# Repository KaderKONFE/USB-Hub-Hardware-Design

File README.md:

# USB Hub Hardware & PCB Design

This repository contains the schematic and PCB design for a high-speed USB Hub, developed according to industrial design rules and signal integrity standards.

## Tech Stack & Tools
* **CAD Software:** KiCad
* **Design Type:** Schematic Capture & PCB Layout
* **Key Focus:** Signal integrity, power management, and protection circuits.

## Features
* Designed high-speed USB data lines with proper impedance matching.
* Integrated power management and circuit protection elements.

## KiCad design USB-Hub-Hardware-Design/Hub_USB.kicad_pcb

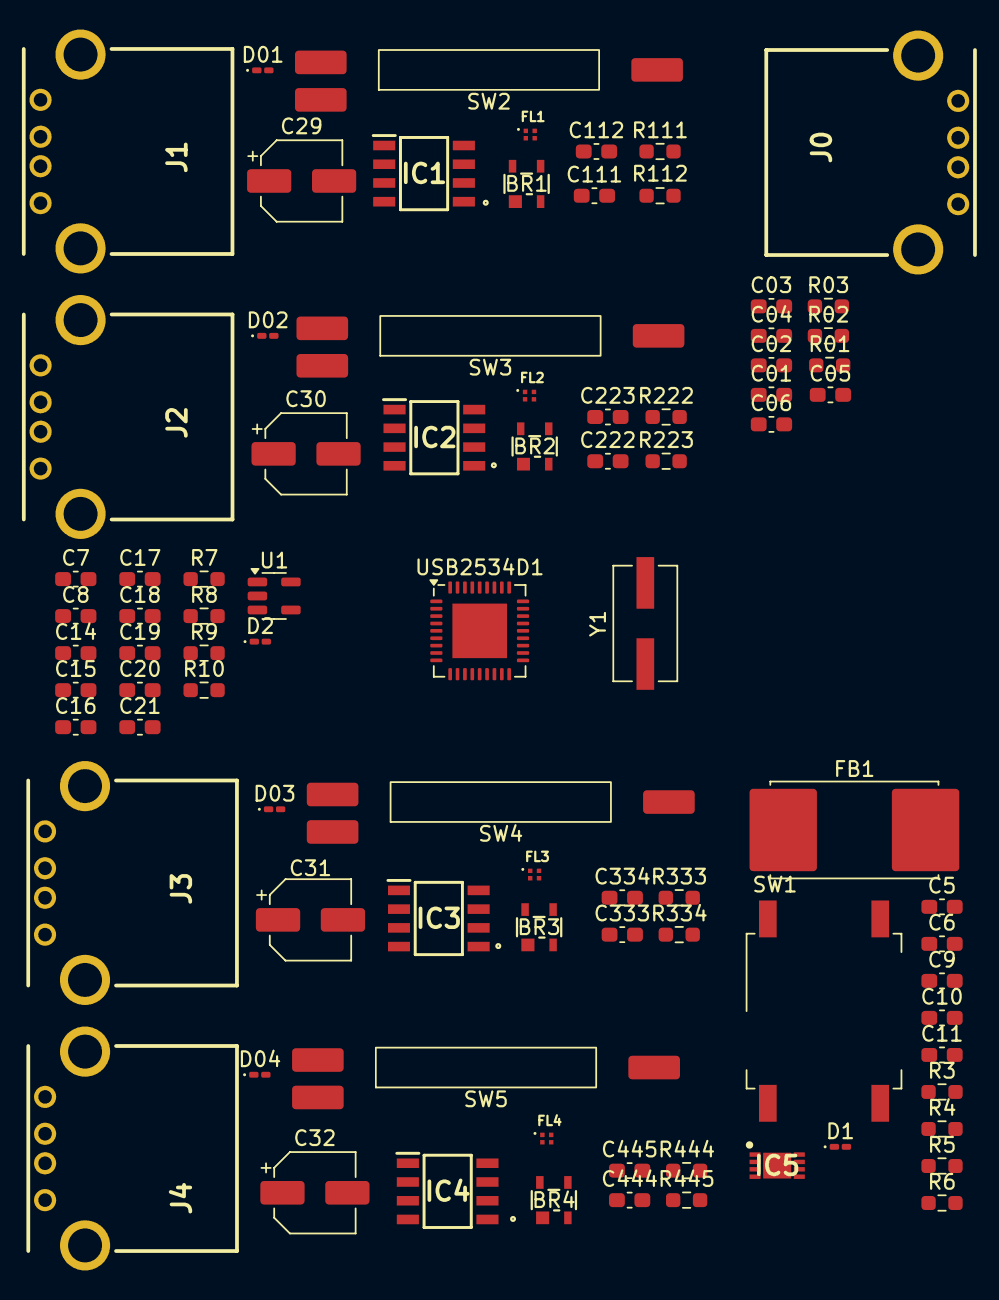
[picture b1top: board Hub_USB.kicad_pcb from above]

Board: 2 copper layers, 85 parts (0 on the bottom side), 45 nets, no tracks yet.

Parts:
BR1, BR2, BR3, BR4: BGX50AE6327HTSA1
C01: 10uF; C_0603_1608Metric_Pad1.08x0.95mm_HandSolder
C02, C5, C06, C6, C14, C16, C17, C19, C20, C111, C112, C222, C223, C333, C334, C444, C445: 0.1uF; C_0603_1608Metric_Pad1.08x0.95mm_HandSolder
C03: 2.2uF; C_0603_1608Metric_Pad1.08x0.95mm_HandSolder
C04: 1nF; C_0603_1608Metric_Pad1.08x0.95mm_HandSolder
C05, C9: 1.0nF; C_0603_1608Metric_Pad1.08x0.95mm_HandSolder
C7, C8: 6pF; C_0603_1608Metric_Pad1.08x0.95mm_HandSolder
C10, C11, C15, C18, C21: 4.7uF; C_0603_1608Metric_Pad1.08x0.95mm_HandSolder
C29, C30, C31, C32: 150uF; CP_Elec_5x5.7
D01, D1, D02, D2, D03, D04: LED; LED_0201_0603Metric_Pad0.64x0.40mm_HandSolder
FB1: 2A/0.05DCR; L_Vishay_IHSM-3825
FL1, FL2, FL3, FL4: DLM0NSM900HY2D
IC1, IC2, IC3, IC4: AP2111SG-13
IC5: MCP1725-ADJE_MC
J0, J1, J2, J3, J4: 614004190021
R01, R3, R111, R112, R222, R223, R333, R334, R444, R445: 330; R_0603_1608Metric_Pad0.98x0.95mm_HandSolder
R02, R10: 100K; R_0603_1608Metric_Pad0.98x0.95mm_HandSolder
R03: 50K; R_0603_1608Metric_Pad0.98x0.95mm_HandSolder
R4: 150K; R_0603_1608Metric_Pad0.98x0.95mm_HandSolder
R5: 21.0K; R_0603_1608Metric_Pad0.98x0.95mm_HandSolder
R6, R8: 10K; R_0603_1608Metric_Pad0.98x0.95mm_HandSolder
R7: 12.0K; R_0603_1608Metric_Pad0.98x0.95mm_HandSolder
R9: 1K; R_0603_1608Metric_Pad0.98x0.95mm_HandSolder
SW1: SW_MEC_5G; SW_MEC_5GSH9
SW2, SW3, SW4, SW5: SW_SPDT; SW_SPDT_REED_MSDM-DT
U1: 74LVC1G14; SOT-23-5
USB2534D1: QFN-36-1EP_6x6mm_P0.5mm_EP3.7x3.7mm
Y1: 24MHz; Crystal_SMD_ECS_CSM3X-2Pin_7.6x4.1mm

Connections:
+3V3: C6.1, C9.1, C11.1, C14.2, C15.2, C16.2, C17.2, C18.2, C19.2, C20.2, IC5.8 (VOUT), R3.1, R4.1, R10.2, U1.3 (GND), USB2534D1.10 (VDDA33), USB2534D1.11 (FLEX_IN), USB2534D1.15 (VDD33), USB2534D1.23 (VDD33), USB2534D1.29 (VDDA33), USB2534D1.36 (VDDA33)
+5V: FB1.1, IC1.2 (IN_1), IC1.3 (IN_2), IC2.2 (IN_1), IC2.3 (IN_2), IC3.2 (IN_1), IC3.3 (IN_2), IC4.2 (IN_1), IC4.3 (IN_2), SW2.2 (B), SW3.2 (B), SW4.2 (B), SW5.2 (B)
/Connectors/EN1: IC1.4 (EN), SW2.1 (A)
/Connectors/EN2: IC2.4 (EN), SW3.1 (A)
/Connectors/EN3: IC3.4 (EN), SW4.1 (A)
/Connectors/EN4: IC4.4 (EN), SW5.1 (A)
/Connectors/PWR1: BR1.1, C29.2, C112.2, IC1.6 (OUT_1), IC1.7 (OUT_2), J1.1, R111.1
/Connectors/PWR2: BR2.1, C30.2, C223.2, IC2.6 (OUT_1), IC2.7 (OUT_2), J2.1, R222.1
/Connectors/PWR3: BR3.1, C31.2, C334.2, IC3.6 (OUT_1), IC3.7 (OUT_2), J3.1, R333.1
/Connectors/PWR4: BR4.1, C32.2, C445.2, IC4.6 (OUT_1), IC4.7 (OUT_2), J4.1, R444.1
/Core/XTAL1: C7.2, USB2534D1.33 (XTAL1/REFCLK), Y1.2
/Core/XTAL2: C8.2, USB2534D1.32 (XTAL2), Y1.1
DWNSTRM1-D_N: BR1.4, FL1.3, FL1.4, J1.2, USB2534D1.1 (SWAP_USBDN1_DM)
DWNSTRM1-D_P: BR1.2, FL1.1, FL1.2, J1.3, USB2534D1.2 (SWAP_USBDN1_DP)
DWNSTRM2-D_N: BR2.4, FL2.3, FL2.4, J2.2, USB2534D1.3 (USBDN2_DM)
DWNSTRM2-D_P: BR2.2, FL2.1, FL2.2, J2.3, USB2534D1.4 (USBDN2_DP)
DWNSTRM3-D_N: BR3.4, FL3.3, FL3.4, J3.2, USB2534D1.6 (USBDN3_DM)
DWNSTRM3-D_P: BR3.2, FL3.1, FL3.2, J3.3, USB2534D1.7 (USBDN3_DP)
DWNSTRM4-D_N: BR4.4, FL4.3, FL4.4, J4.2, USB2534D1.8 (USBDN4_DM)
DWNSTRM4-D_P: BR4.2, FL4.1, FL4.2, J4.3, USB2534D1.9 (USBDN4_DP)
GND: BR1.3, BR2.3, BR3.3, BR4.3, C01.2, C02.2, C03.2, C04.2, C5.2, C06.1, C6.2, C7.1, C8.1, C9.2, C10.2, C11.2, C14.1, C15.1, C16.1, C17.1, C18.1, C19.1, C20.1, C21.1, C111.1, C112.1, C222.1, C223.1, C333.1, C334.1, C444.1, C445.1, D01.1 (K), D1.1 (K), D02.1 (K), D2.1 (K), D03.1 (K), D04.1 (K), IC1.1 (GND), IC2.1 (GND), IC3.1 (GND), IC4.1 (GND), IC5.4 (GND), IC5.9 (EP), J0.5, J0.6, J1.5, J1.6, J2.5, J2.6, J3.5, J3.6, J4.5, J4.6, R01.1, R02.1, R5.2, R7.1, R8.1, R112.1, R223.1, R334.1, R445.1, SW1.1 (A), SW1.2 (A), U1.5 (VCC), USB2534D1.28 (GND), USB2534D1.37 (EP)
GNDPWR: C05.1, C06.2, C29.1, C30.1, C31.1, C32.1, C111.2, C222.2, C333.2, C444.2, J0.4, J1.4, J2.4, J3.4, J4.4, R01.2, R112.2, R223.2, R334.2, R445.2
unnamed: C01.1, C02.1, C03.1, C05.2, J0.1, R03.1
unnamed: D01.2 (A), R111.2
unnamed: D1.2 (A), R3.2
unnamed: D02.2 (A), R222.2
unnamed: D2.2 (A), R9.1
unnamed: D03.2 (A), R333.2
unnamed: D04.2 (A), R444.2
unnamed: IC5.7 (ADJ), R4.2, R5.1
unnamed: C5.1, IC5.6 (CDELAY), SW1.3 (B), SW1.4 (B)
unnamed: C10.1, FB1.2, IC5.1 (VIN_1), IC5.2 (VIN_2), R6.1
unnamed: IC5.3 (~SHDN), R6.2
unnamed: R9.2, U1.4
unnamed: R7.2, USB2534D1.35 (RBIAS)
unnamed: R8.2, USB2534D1.25 (TEST)
unnamed: C21.2, USB2534D1.14 (VDDCR14)
OCS1: IC1.5 (FLG), USB2534D1.13 (~OCS1_N)
OCS2: IC2.5 (FLG), USB2534D1.17 (~OCS2_N)
OCS3: IC3.5 (FLG), USB2534D1.19 (UART_RX/~OCS3_N)
OCS4: IC4.5 (FLG), USB2534D1.21 (UART_TX/~OCS4_N)
PWRGD: IC5.5 (PWRGD), R10.1, U1.2, USB2534D1.26 (~RESET_N)
UPSTRM0-D_N: J0.2, USB2534D1.30 (FLEX_USBUP_DM)
UPSTRM0-D_P: J0.3, USB2534D1.31 (FLEX_USBUP_DP)
VBUS_DET: C04.1, R02.2, R03.2, USB2534D1.27 (VBUS_DET)

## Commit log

2026-06-27 Add KiCad schematic and PCB layout files
2026-06-27 Revise README with project overview and features
    Updated project title and added project details, tech stack, and features.
